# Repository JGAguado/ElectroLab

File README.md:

[![Documentation Status][documentation-shield]][documentation]
[![GitHub Release][releases-shield]][releases]
[![License][license-shield]](LICENSE)
[![BuyIt][buyit-shield]][elecrow]

[![Project Maintenance][maintenance-shield]][maintenance]
[![BuyMeCoffee][buymecoffee-shield]][buymecoffee]

# ElectroLab

The ElectroLab board is an electronic trainer designed for educational purposes. It should be considered as a beginner-friendly guided solution for learning practical electronics where no prior knowledge is required.

With its big set of integrated components, the ElectroLab offers a very powerful and versatile platform for building up your electronic circuits in very few steps.

[documentation-shield]: https://readthedocs.org/projects/electrolab/badge/?version=latest&style=for-the-badge
[documentation]: https://electrolab.readthedocs.io/en/v3/

[releases-shield]: https://img.shields.io/github/release/JGAguado/ElectroLab.svg?style=for-the-badge
[releases]: https://github.com/JGAguado/ElectroLab/releases

[license-shield]: https://img.shields.io/badge/License-CC%20BY--NC--SA%204.0-lightgrey.svg?style=for-the-badge

[maintenance-shield]: https://img.shields.io/badge/maintainer-J.%20G.%20Aguado-blue.svg?style=for-the-badge
[maintenance]: https://github.com/JGAguado

[buymecoffee-shield]: https://img.shields.io/badge/buy%20me%20a%20coffee-support-yellow.svg?style=for-the-badge
[buymecoffee]: https://www.buymeacoffee.com/J.G.Aguado

[buyit-shield]: https://img.shields.io/badge/get%20it%20on-elecrow-399BD7.svg?style=for-the-badge
[elecrow]: https://www.elecrow.com/electrolab.html

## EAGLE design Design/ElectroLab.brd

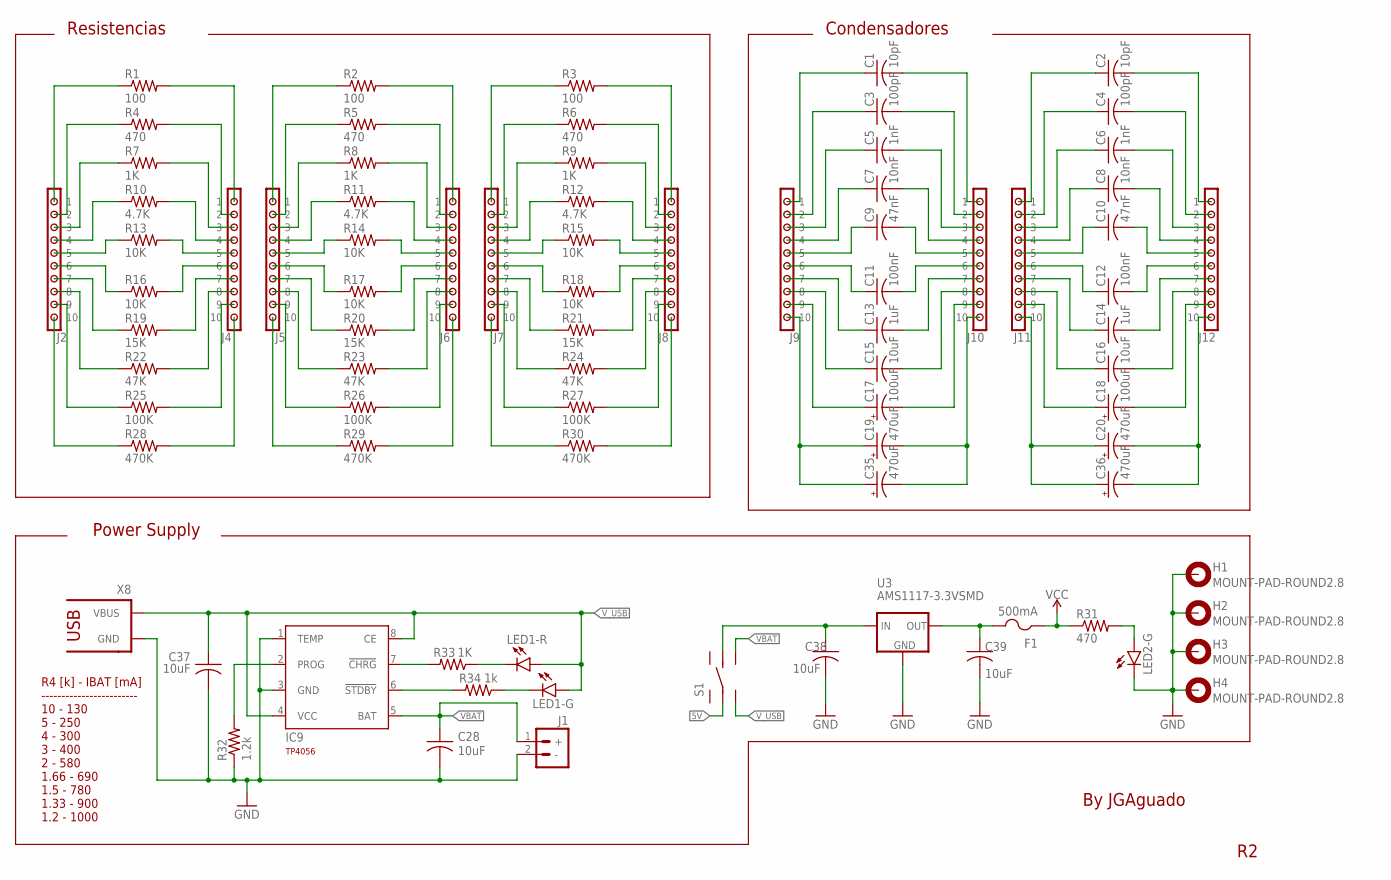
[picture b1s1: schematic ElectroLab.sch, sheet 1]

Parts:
C1, C2: 10pF; 0603
C3, C4: 100pF; 0603
C5, C6: 1nF; 0603
C7, C8: 10nF; 0603
C9, C10: 47nF; 0603
C11, C12: 100nF; 0603
C13, C14: 1uF; 0603
C15, C16: 10uF; 0603
C17, C18: 100uF; B/3528-21R; LCSC C16133
C19, C20, C35, C36: 470uF; D/7343-31R
C28, C37, C38, C39: 10uF; C0603
F1: 500mA; R1206; LCSC C355568
H1, H2, H3, H4: MOUNT-PAD-ROUND2.8; 2,8-PAD
IC9: TP4056; SOT23-8; LCSC C16581
J1: BAT_CONN-JST-2MM-SMT; JST-2-SMD; LCSC C3029440
J2, J4, J5, J6, J7, J8, J9, J10, J11, J12: CONN_10"; 1X10
LED1, LED2: E6CC1205RYGC2UDA; BICOLOR_LED
R1, R2, R3: 100; 0603
R4, R5, R6, R31: 470; 0603
R7, R8, R9, R33: 1K; 0603
R10, R11, R12: 4.7K; 0603
R13, R14, R15, R16, R17, R18: 10K; 0603
R19, R20, R21: 15K; 0603
R22, R23, R24: 47K; 0603
R25, R26, R27: 100K; 0603
R28, R29, R30: 470K; 0603
R32: 1.2k; R0603
R34: 1k; 0603
S1: DPDT_JS202011CQN
U3: AMS1117-3.3VSMD; SOT223
X8: USB-C-POWER

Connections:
5V: S1.2 (LC); also elsewhere on the board
GND: C28.2, C37.2, C38.2, C39.2, H1.B2,8, H2.B2,8, H3.B2,8, H4.B2,8, IC9.1 (TEMP), IC9.3 (GND), J1.2 (-), LED2.1 (C), R32.1, U3.1 (GND), X8.GND; also elsewhere on the board
unnamed: J2.1, R1.1
unnamed: J2.2, R4.1
unnamed: J2.3, R7.1
unnamed: J2.4, R10.1
unnamed: J2.5, R13.1
unnamed: J2.6, R16.1
unnamed: J2.7, R19.1
unnamed: J2.8, R22.1
unnamed: J2.9, R25.1
unnamed: J2.10, R28.1
unnamed: J4.10, R28.2
unnamed: J4.9, R25.2
unnamed: J4.8, R22.2
unnamed: J4.7, R19.2
unnamed: J4.5, R13.2
unnamed: J4.6, R16.2
unnamed: J4.4, R10.2
unnamed: J4.3, R7.2
unnamed: J4.2, R4.2
unnamed: J4.1, R1.2
unnamed: J5.1, R2.1
unnamed: J5.2, R5.1
unnamed: J5.3, R8.1
unnamed: J5.4, R11.1
unnamed: J5.5, R14.1
unnamed: J5.6, R17.1
unnamed: J5.7, R20.1
unnamed: J5.8, R23.1
unnamed: J5.9, R26.1
unnamed: J5.10, R29.1
unnamed: J6.10, R29.2
unnamed: J6.9, R26.2
unnamed: J6.8, R23.2
unnamed: J6.7, R20.2
unnamed: J6.6, R17.2
unnamed: J6.5, R14.2
unnamed: J6.4, R11.2
unnamed: J6.3, R8.2
unnamed: J6.2, R5.2
unnamed: J6.1, R2.2
unnamed: J7.1, R3.1
unnamed: J7.2, R6.1
unnamed: J7.3, R9.1
unnamed: J7.4, R12.1
unnamed: J7.5, R15.1
unnamed: J7.6, R18.1
unnamed: J7.7, R21.1
unnamed: J7.8, R24.1
unnamed: J7.9, R27.1
unnamed: J7.10, R30.1
unnamed: J8.10, R30.2
unnamed: J8.9, R27.2
unnamed: J8.8, R24.2
unnamed: J8.7, R21.2
unnamed: J8.6, R18.2
unnamed: J8.5, R15.2
unnamed: J8.4, R12.2
unnamed: J8.3, R9.2
unnamed: J8.2, R6.2
unnamed: J8.1, R3.2
unnamed: C1.1, J9.1
unnamed: C3.1, J9.2
unnamed: C5.1, J9.3
unnamed: C7.1, J9.4
unnamed: C9.1, J9.5
unnamed: C11.1, J9.6
unnamed: C13.1, J9.7
unnamed: C15.1, J9.8
unnamed: C17.+, J9.9
unnamed: C19.+, C35.+, J9.10
unnamed: C1.2, J10.1
unnamed: C3.2, J10.2
unnamed: C5.2, J10.3
unnamed: C7.2, J10.4
unnamed: C9.2, J10.5
unnamed: C11.2, J10.6
unnamed: C13.2, J10.7
unnamed: C15.2, J10.8
unnamed: C17.-, J10.9
unnamed: C19.-, C35.-, J10.10
unnamed: C2.1, J11.1
unnamed: C4.1, J11.2
unnamed: C6.1, J11.3
unnamed: C8.1, J11.4
unnamed: C10.1, J11.5
unnamed: C12.1, J11.6
unnamed: C14.1, J11.7
unnamed: C16.1, J11.8
unnamed: C18.+, J11.9
unnamed: C20.+, C36.+, J11.10
unnamed: C20.-, C36.-, J12.10
unnamed: C18.-, J12.9
unnamed: C16.2, J12.8
unnamed: C14.2, J12.7
unnamed: C12.2, J12.6
unnamed: C10.2, J12.5
unnamed: C8.2, J12.4
unnamed: C6.2, J12.3
unnamed: C4.2, J12.2
unnamed: C2.2, J12.1
unnamed: LED2.2 (A), R31.2
unnamed: IC9.6 (!STDBY), R34.2
unnamed: LED1.4 (C), R33.1
unnamed: LED1.1 (C), R34.1
unnamed: IC9.2 (PROG), R32.2
unnamed: IC9.7 (!CHRG), R33.2
unnamed: C38.1, S1.5 (RC), U3.3 (IN)
VBAT: C28.1, IC9.5 (BAT), J1.1 (+), S1.6 (R2)
VCC: F1.1, R31.1; also elsewhere on the board
VOUT: C39.1, F1.2, U3.2 (OUT)
V_USB: C37.1, IC9.4 (VCC), IC9.8 (CE), LED1.2 (A), LED1.3 (A), S1.3 (L2), X8.VBUS

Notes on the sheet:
By JGAguado
Condensadores
Resistencias
Power Supply
R4 [k] - IBAT [mA] ------------------------ 10 - 130 5 - 250 4 - 300 3 - 400 2 - 580 1.66 - 690 1.5 - 780 1.33 - 900 1.2 - 1000

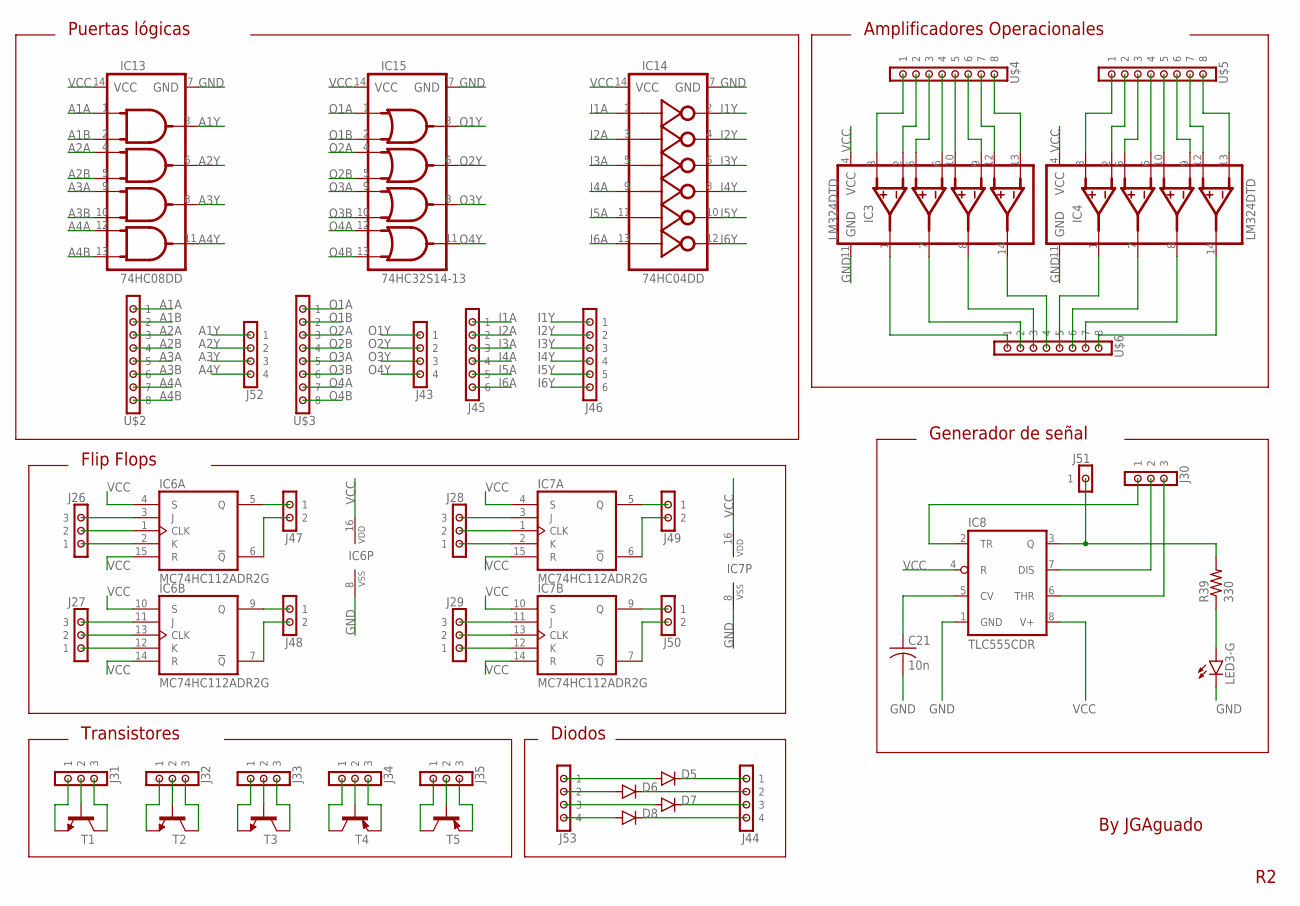
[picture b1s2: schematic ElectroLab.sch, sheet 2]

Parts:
C21: 10n; 0603
D5, D6, D7, D8: LL4148; LL-34
IC3, IC4: LM324DTD; SO14
IC6, IC7: MC74HC112ADR2G; SO16
IC8: TLC555CDR; SO08; LCSC C6986
IC13: 74HC08DD; SO14
IC14: 74HC04DD; SO14
IC15: 74HC32S14-13; SO14; LCSC C176921
J26, J27, J28, J29, J30, J31, J32, J33, J34, J35: CONN_03; 1X03
J43, J44, J52, J53: CONN_04; 1X04
J45, J46: CONN_06; 1X06
J47, J48, J49, J50: CONN_02; 1X02
J51: CONN_01; 1X01
LED3: E6CC1205RYGC2UDA; BICOLOR_LED
R39: 330; 0603
T1: MMBT2222A; SOT23
T2, T3: T_NPNMMBT2222A-1P_CHANGJ_SOT23-BEC; SOT23
T4, T5: T_PNPMMBT5401_CHANGJ_SOT23-BEC; SOT23
U$2, U$3, U$4, U$5, U$6: CONN_08; 1X08

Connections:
A1A: IC13.1 (1A), U$2.1; also elsewhere on the board
A1B: IC13.2 (1B), U$2.2; also elsewhere on the board
A1Y: IC13.3 (1Y), J52.1
A2A: IC13.4 (2A), U$2.3; also elsewhere on the board
A2B: IC13.5 (2B), U$2.4; also elsewhere on the board
A2Y: IC13.6 (2Y), J52.2
A3A: IC13.9 (3A), U$2.5; also elsewhere on the board
A3B: IC13.10 (3B), U$2.6; also elsewhere on the board
A3Y: IC13.8 (3Y), J52.3
A4A: IC13.12 (4A), U$2.7; also elsewhere on the board
A4B: IC13.13 (4B), U$2.8; also elsewhere on the board
A4Y: IC13.11 (4Y), J52.4
GND: C21.2, IC3.11 (GND), IC4.11 (GND), IC6.8 (VSS), IC7.8 (VSS), IC8.1 (GND), IC13.7 (GND), IC14.7 (GND), IC15.7 (GND), LED3.1 (C); also elsewhere on the board
I1A: IC14.1 (1A), J45.1; also elsewhere on the board
I1Y: IC14.2 (1Y), J46.1
I2A: IC14.3 (2A), J45.2; also elsewhere on the board
I2Y: IC14.4 (2Y), J46.2
I3A: IC14.5 (3A), J45.3; also elsewhere on the board
I3Y: IC14.6 (3Y), J46.3
I4A: IC14.9 (4A), J45.4; also elsewhere on the board
I4Y: IC14.8 (4Y), J46.4
I5A: IC14.11 (5A), J45.5; also elsewhere on the board
I5Y: IC14.10 (5Y), J46.5
I6A: IC14.13 (6A), J45.6; also elsewhere on the board
I6Y: IC14.12 (6Y), J46.6
unnamed: D8.A, J53.4
unnamed: D8.C, J44.4
unnamed: D5.A, J53.1
unnamed: IC6.5 (Q), J47.1
unnamed: IC6.9 (Q), J48.1
unnamed: IC7.5 (Q), J49.1
unnamed: IC7.9 (Q), J50.1
unnamed: LED3.2 (A), R39.1
unnamed: IC3.3 (1+), U$4.1
unnamed: IC3.2 (1-), U$4.2
unnamed: IC3.5 (2+), U$4.3
unnamed: IC3.6 (2-), U$4.4
unnamed: IC3.10 (3+), U$4.5
unnamed: IC3.9 (3-), U$4.6
unnamed: IC3.12 (4+), U$4.7
unnamed: IC3.13 (4-), U$4.8
unnamed: IC4.3 (1+), U$5.1
unnamed: IC6.2 (K), J26.1
unnamed: IC6.1 (CLK), J26.2
unnamed: IC6.3 (J), J26.3
unnamed: IC6.12 (K), J27.1
unnamed: IC6.13 (CLK), J27.2
unnamed: IC6.11 (J), J27.3
unnamed: IC7.2 (K), J28.1
unnamed: IC7.1 (CLK), J28.2
unnamed: IC7.3 (J), J28.3
unnamed: IC7.12 (K), J29.1
unnamed: IC7.13 (CLK), J29.2
unnamed: IC7.11 (J), J29.3
unnamed: IC6.6 (!Q), J47.2
unnamed: IC6.7 (!Q), J48.2
unnamed: IC7.6 (!Q), J49.2
unnamed: IC7.7 (!Q), J50.2
unnamed: D7.A, J53.3
unnamed: D6.A, J53.2
unnamed: IC4.2 (1-), U$5.2
unnamed: IC4.5 (2+), U$5.3
unnamed: IC4.6 (2-), U$5.4
unnamed: IC4.10 (3+), U$5.5
unnamed: IC4.9 (3-), U$5.6
unnamed: IC4.12 (4+), U$5.7
unnamed: IC4.13 (4-), U$5.8
unnamed: IC3.1 (1Y), U$6.1
unnamed: IC3.7 (2Y), U$6.2
unnamed: IC3.8 (3Y), U$6.3
unnamed: IC3.14 (4Y), U$6.4
unnamed: IC4.1 (1Y), U$6.5
unnamed: IC4.7 (2Y), U$6.6
unnamed: D5.C, J44.1
unnamed: IC4.8 (3Y), U$6.7
unnamed: IC4.14 (4Y), U$6.8
unnamed: D6.C, J44.2
unnamed: D7.C, J44.3
unnamed: J31.1, T1.2 (E)
unnamed: J31.2, T1.1 (B)
unnamed: J31.3, T1.3 (C)
unnamed: J32.1, T2.2 (E)
unnamed: J32.2, T2.1 (B)
unnamed: J32.3, T2.3 (C)
unnamed: J33.1, T3.2 (E)
unnamed: J33.2, T3.1 (B)
unnamed: J33.3, T3.3 (C)
unnamed: J34.1, T4.3 (C)
unnamed: J34.2, T4.1 (B)
unnamed: J34.3, T4.2 (E)
unnamed: J35.1, T5.3 (C)
unnamed: J35.2, T5.1 (B)
unnamed: J35.3, T5.2 (E)
unnamed: IC8.2 (TR), J30.1
unnamed: IC8.3 (Q), J51.1, R39.2
unnamed: C21.1, IC8.5 (CV)
unnamed: IC8.7 (DIS), J30.2
unnamed: IC8.6 (THR), J30.3
O1A: IC15.1 (1A), U$3.1; also elsewhere on the board
O1B: IC15.2 (1B), U$3.2; also elsewhere on the board
O1Y: IC15.3 (1Y), J43.1
O2A: IC15.4 (2A), U$3.3; also elsewhere on the board
O2B: IC15.5 (2B), U$3.4; also elsewhere on the board
O2Y: IC15.6 (2Y), J43.2
O3A: IC15.9 (3A), U$3.5; also elsewhere on the board
O3B: IC15.10 (3B), U$3.6; also elsewhere on the board
O3Y: IC15.8 (3Y), J43.3
O4A: IC15.12 (4A), U$3.7; also elsewhere on the board
O4B: IC15.13 (4B), U$3.8; also elsewhere on the board
O4Y: IC15.11 (4Y), J43.4
VCC: IC3.4 (VCC), IC4.4 (VCC), IC6.4 (S), IC6.10 (S), IC6.14 (R), IC6.15 (R), IC6.16 (VDD), IC7.4 (S), IC7.10 (S), IC7.14 (R), IC7.15 (R), IC7.16 (VDD), IC8.4 (R), IC8.8 (V+), IC13.14 (VCC), IC14.14 (VCC), IC15.14 (VCC); also elsewhere on the board

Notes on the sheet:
Puertas lógicas
Amplificadores Operacionales
Flip Flops
Transistores
Diodos
Generador de señal
By JGAguado

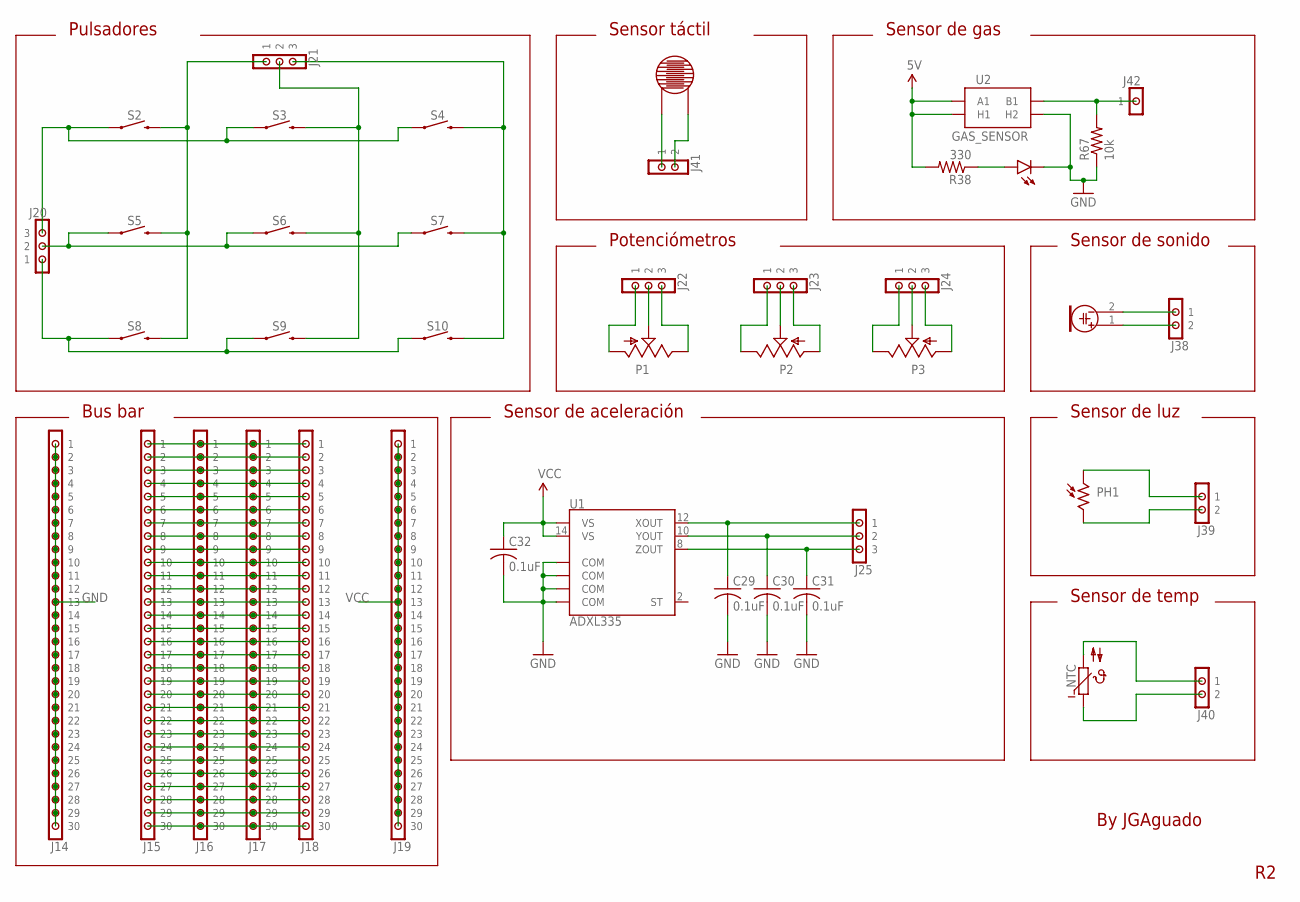
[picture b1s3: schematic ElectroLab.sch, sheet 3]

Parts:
C29, C30, C31, C32: 0.1uF; 0603
J14, J15, J16, J17, J18, J19: CONN_30; 1X30
J20, J21, J22, J23, J24, J25: CONN_03; 1X03
J38, J39, J40, J41: CONN_02; 1X02
J42: CONN_01; 1X01
LED13: E6CC1205RYGC2UDA; BICOLOR_LED
MIC: MICROPHONE
NTC: THERMISTOR; NTC
P1: SLIDE_POT_20MM; RS201111J011
P2, P3: ALPS_RK09K_VERTICAL
PH1: PHOTORESISTOR; GL5516
R38: 330; 0603
R67: 10k; 0603
S2, S3, S4, S5, S6, S7, S8, S9, S10: MOMENTARY-SWITCH-SPST-PTH-6.0MM; TACTILE_SWITCH_PTH_6.0MM
U1: ADXL335; LFCSP-16-4X4; LCSC C34439
U2: GAS_SENSOR
U$16: RESISTIVE_SENSOR_PAD

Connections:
5V: R38.2, U2.A1, U2.HA (H1); also elsewhere on the board
GND: C29.2, C30.2, C31.2, C32.2, J14.1, J14.2, J14.3, J14.4, J14.5, J14.6, J14.7, J14.8, J14.9, J14.10, J14.11, J14.12, J14.13, J14.14, J14.15, J14.16, J14.17, J14.18, J14.19, J14.20, J14.21, J14.22, J14.23, J14.24, J14.25, J14.26, J14.27, J14.28, J14.29, J14.30, LED13.1 (C), R67.1, U1.3 (COM), U1.5 (COM), U1.6 (COM), U1.7 (COM), U2.HB (H2); also elsewhere on the board
unnamed: J42.1, R67.2, U2.B1
unnamed: LED13.2 (A), R38.1
unnamed: J41.2, U$16.0
unnamed: J41.1, U$16.1
unnamed: J15.24, J16.24, J17.24, J18.24
unnamed: J15.30, J16.30, J17.30, J18.30
unnamed: J15.29, J16.29, J17.29, J18.29
unnamed: J15.28, J16.28, J17.28, J18.28
unnamed: J15.27, J16.27, J17.27, J18.27
unnamed: J15.26, J16.26, J17.26, J18.26
unnamed: J15.25, J16.25, J17.25, J18.25
unnamed: J15.23, J16.23, J17.23, J18.23
unnamed: J15.22, J16.22, J17.22, J18.22
unnamed: J15.21, J16.21, J17.21, J18.21
unnamed: J15.20, J16.20, J17.20, J18.20
unnamed: J15.19, J16.19, J17.19, J18.19
unnamed: J15.18, J16.18, J17.18, J18.18
unnamed: J15.17, J16.17, J17.17, J18.17
unnamed: J15.16, J16.16, J17.16, J18.16
unnamed: J15.15, J16.15, J17.15, J18.15
unnamed: J15.14, J16.14, J17.14, J18.14
unnamed: J15.13, J16.13, J17.13, J18.13
unnamed: J15.12, J16.12, J17.12, J18.12
unnamed: J15.11, J16.11, J17.11, J18.11
unnamed: J15.10, J16.10, J17.10, J18.10
unnamed: J15.9, J16.9, J17.9, J18.9
unnamed: J15.8, J16.8, J17.8, J18.8
unnamed: J15.7, J16.7, J17.7, J18.7
unnamed: J15.6, J16.6, J17.6, J18.6
unnamed: J15.5, J16.5, J17.5, J18.5
unnamed: J15.4, J16.4, J17.4, J18.4
unnamed: J15.3, J16.3, J17.3, J18.3
unnamed: J15.2, J16.2, J17.2, J18.2
unnamed: J15.1, J16.1, J17.1, J18.1
unnamed: J21.1, S2.3 (2), S5.3 (2), S8.3 (2)
unnamed: J21.2, S3.3 (2), S6.3 (2), S9.3 (2)
unnamed: J39.1, PH1.1
unnamed: J39.2, PH1.3
unnamed: J40.1, NTC.2
unnamed: J23.1, P2.3
unnamed: J23.2, P2.2
unnamed: J23.3, P2.1
unnamed: J22.1, P1.3
unnamed: J22.2, P1.2
unnamed: J22.3, P1.1
unnamed: J24.1, P3.3
unnamed: J24.2, P3.2
unnamed: J24.3, P3.1
unnamed: J38.1, MIC.2
unnamed: J38.2, MIC.1
unnamed: J20.3, S2.1, S3.1, S4.1
unnamed: J40.2, NTC.1
unnamed: J20.2, S5.1, S6.1, S7.1
unnamed: J21.3, S4.3 (2), S7.3 (2), S10.3 (2)
unnamed: J20.1, S8.1, S9.1, S10.1
VCC: C32.1, J19.1, J19.2, J19.3, J19.4, J19.5, J19.6, J19.7, J19.8, J19.9, J19.10, J19.11, J19.12, J19.13, J19.14, J19.15, J19.16, J19.17, J19.18, J19.19, J19.20, J19.21, J19.22, J19.23, J19.24, J19.25, J19.26, J19.27, J19.28, J19.29, J19.30, U1.14 (VS), U1.15 (VS); also elsewhere on the board
X+: C29.1, J25.1, U1.12 (XOUT)
Y+: C30.1, J25.2, U1.10 (YOUT)
Z+: C31.1, J25.3, U1.8 (ZOUT)

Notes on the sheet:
Pulsadores
Potenciómetros
Sensor táctil
Sensor de luz
Sensor de sonido
Sensor de temp
Sensor de aceleración
Bus bar
By JGAguado
Sensor de gas

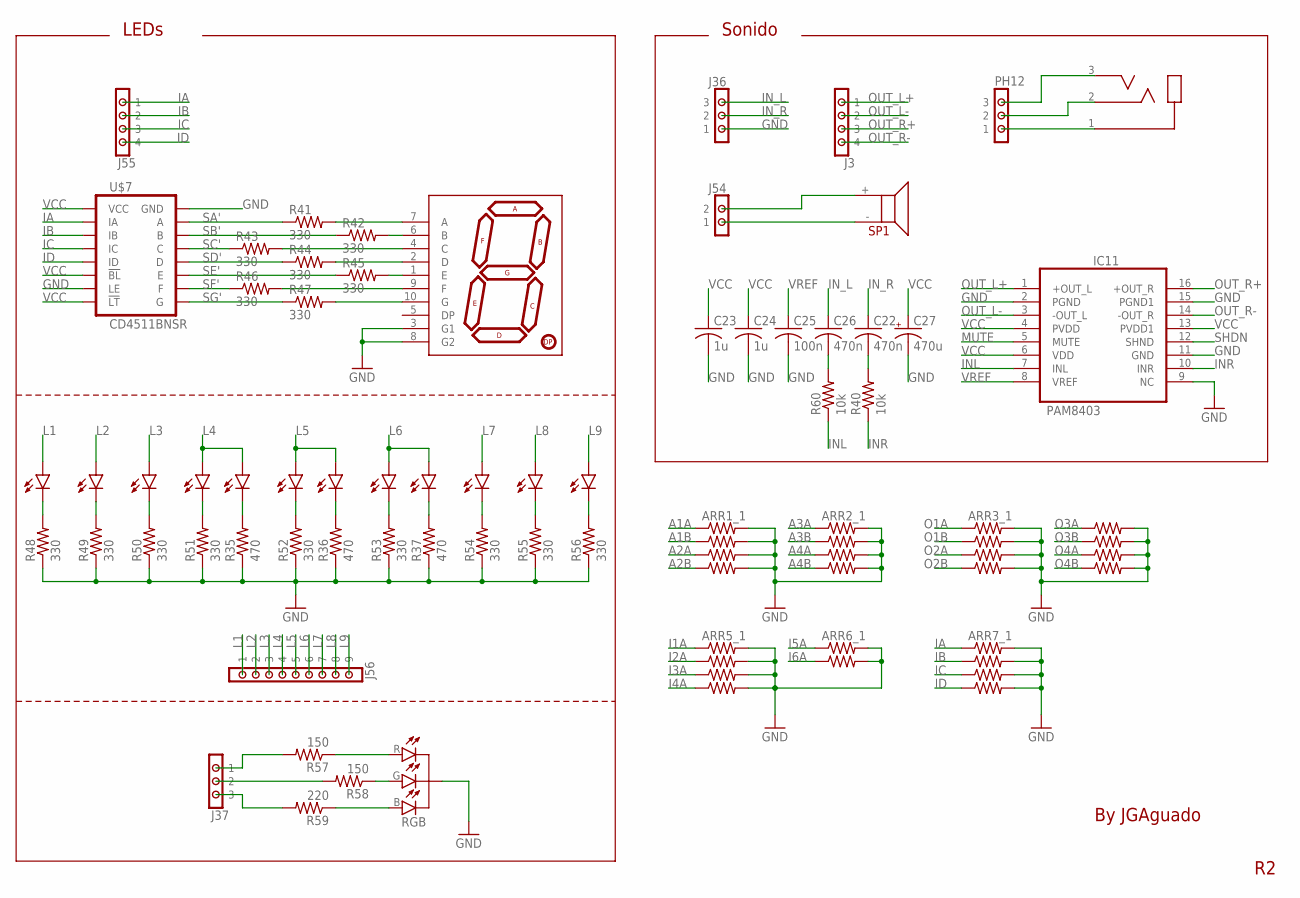
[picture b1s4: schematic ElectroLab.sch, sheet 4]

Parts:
ARR1, ARR2, ARR3, ARR4, ARR5, ARR6, ARR7: 4_RES_ARRAY_R06031KOHM; 0603-ARC
C22, C26: 470n; 0603
C23, C24: 1u; 0603
C25: 100n; 0603
C27: 470u; D/7343-31R; LCSC C7229
IC11: PAM8403; SOP-16
J3, J55: CONN_04; 1X04
J36, J37: CONN_03; 1X03
J54: CONN_02; 1X02
J56: CONN_09; 1X09
JACK: AUDIO_JACK_MONO_3.5_3P; HC-PJ-320A-3P-D
LED4, LED5, LED6, LED7, LED8, LED9, LED10, LED11, LED12: E6CC1205RYGC2UDA; BICOLOR_LED
PH12: CONN_03; 1X03
R35, R36, R37: 470; 0603
R40, R60: 10k; 0603
R41, R42, R43, R44, R45, R46, R47, R48, R49, R50, R51, R52, R53, R54, R55, R56: 330; 0603
R57, R58: 150; 0603
R59: 220; 0603
RGB: CLEAR; LED-RGB-THRU
SP1: SPEAKERFS1508MB0810-H8.0; FS1508MB0810-H8.0
U$1: FJ5101AG; 7-SEGMENT
U$7: CD4511BNSR; SO16

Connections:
A1A: ARR1.1; also elsewhere on the board
A1B: ARR1.2 (1); also elsewhere on the board
A2A: ARR1.3 (1); also elsewhere on the board
A2B: ARR1.4 (1); also elsewhere on the board
A3A: ARR2.1; also elsewhere on the board
A3B: ARR2.2 (1); also elsewhere on the board
A4A: ARR2.3 (1); also elsewhere on the board
A4B: ARR2.4 (1); also elsewhere on the board
B: J37.3, R59.2
G: J37.2, R58.2
GND: ARR1.5 (2), ARR1.6 (2), ARR1.7 (2), ARR1.8 (2), ARR2.5 (2), ARR2.6 (2), ARR2.7 (2), ARR2.8 (2), ARR3.5 (2), ARR3.6 (2), ARR3.7 (2), ARR3.8 (2), ARR4.5 (2), ARR4.6 (2), ARR4.7 (2), ARR4.8 (2), ARR5.5 (2), ARR5.6 (2), ARR5.7 (2), ARR5.8 (2), ARR6.7 (2), ARR6.8 (2), ARR7.5 (2), ARR7.6 (2), ARR7.7 (2), ARR7.8 (2), C23.2, C24.2, C25.2, C27.-, IC11.2 (PGND), IC11.9 (NC), IC11.11 (GND), IC11.15 (PGND1), J36.1, R35.1, R36.1, R37.1, R48.1, R49.1, R50.1, R51.1, R52.1, R53.1, R54.1, R55.1, R56.1, RGB.C, U$1.3 (G1), U$1.8 (G2), U$7.5 (LE), U$7.8 (GND); also elsewhere on the board
I1A: ARR5.1; also elsewhere on the board
I2A: ARR5.2 (1); also elsewhere on the board
I3A: ARR5.3 (1); also elsewhere on the board
I4A: ARR5.4 (1); also elsewhere on the board
I5A: ARR6.1; also elsewhere on the board
I6A: ARR6.2 (1); also elsewhere on the board
IA: ARR7.1, J55.1, U$7.7 (IA)
IB: ARR7.2 (1), J55.2, U$7.1 (IB)
IC: ARR7.3 (1), J55.3, U$7.2 (IC)
ID: ARR7.4 (1), J55.4, U$7.6 (ID)
INL: IC11.7 (INL), R60.1
INR: IC11.10 (INR), R40.1
IN_L: C26.1, J36.3
IN_R: C22.1, J36.2
L1: J56.1, LED4.2 (A)
L2: J56.2, LED5.2 (A)
L3: J56.3, LED6.2 (A)
L4: J56.4, LED7.2 (A), LED7.3 (A)
L5: J56.5, LED8.2 (A), LED8.3 (A)
L6: J56.6, LED9.2 (A), LED9.3 (A)
L7: J56.7, LED10.3 (A)
L8: J56.8, LED11.3 (A)
L9: J56.9, LED12.3 (A)
MUTE: IC11.5 (MUTE)
unnamed: JACK.2, PH12.2
unnamed: JACK.1, PH12.1
unnamed: R58.1, RGB.G
unnamed: LED4.1 (C), R48.2
unnamed: C26.2, R60.2
unnamed: C22.2, R40.2
unnamed: LED5.1 (C), R49.2
unnamed: LED6.1 (C), R50.2
unnamed: LED7.1 (C), R51.2
unnamed: LED8.1 (C), R52.2
unnamed: LED9.1 (C), R53.2
unnamed: LED7.4 (C), R35.2
unnamed: LED8.4 (C), R36.2
unnamed: LED9.4 (C), R37.2
unnamed: LED10.4 (C), R54.2
unnamed: LED11.4 (C), R55.2
unnamed: LED12.4 (C), R56.2
unnamed: J54.2, SP1.+
unnamed: JACK.3, PH12.3
unnamed: J54.1, SP1.-
unnamed: R57.1, RGB.R
unnamed: R59.1, RGB.B
O1A: ARR3.1; also elsewhere on the board
O1B: ARR3.2 (1); also elsewhere on the board
O2A: ARR3.3 (1); also elsewhere on the board
O2B: ARR3.4 (1); also elsewhere on the board
O3A: ARR4.1; also elsewhere on the board
O3B: ARR4.2 (1); also elsewhere on the board
O4A: ARR4.3 (1); also elsewhere on the board
O4B: ARR4.4 (1); also elsewhere on the board
OUT_L+: IC11.1 (+OUT_L), J3.1
OUT_L-: IC11.3 (-OUT_L), J3.2
OUT_R+: IC11.16 (+OUT_R), J3.3
OUT_R-: IC11.14 (-OUT_R), J3.4
R: J37.1, R57.2
SA: R41.2, U$1.7 (A)
SA': R41.1, U$7.13 (A)
SB: R42.2, U$1.6 (B)
SB': R42.1, U$7.12 (B)
SC: R43.2, U$1.4 (C)
SC': R43.1, U$7.11 (C)
SD: R44.2, U$1.2 (D)
SD': R44.1, U$7.10 (D)
SE: R45.2, U$1.1 (E)
SE': R45.1, U$7.9 (E)
SF: R46.2, U$1.9 (F)
SF': R46.1, U$7.15 (F)
SG: R47.2, U$1.10 (G)
SG': R47.1, U$7.14 (G)
SHDN: IC11.12 (SHND)
VCC: C23.1, C24.1, C27.+, IC11.4 (PVDD), IC11.6 (VDD), IC11.13 (PVDD1), U$7.3 (!LT), U$7.4 (!BL), U$7.16 (VCC); also elsewhere on the board
VREF: C25.1, IC11.8 (VREF)

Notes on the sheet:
Sonido
LEDs
By JGAguado

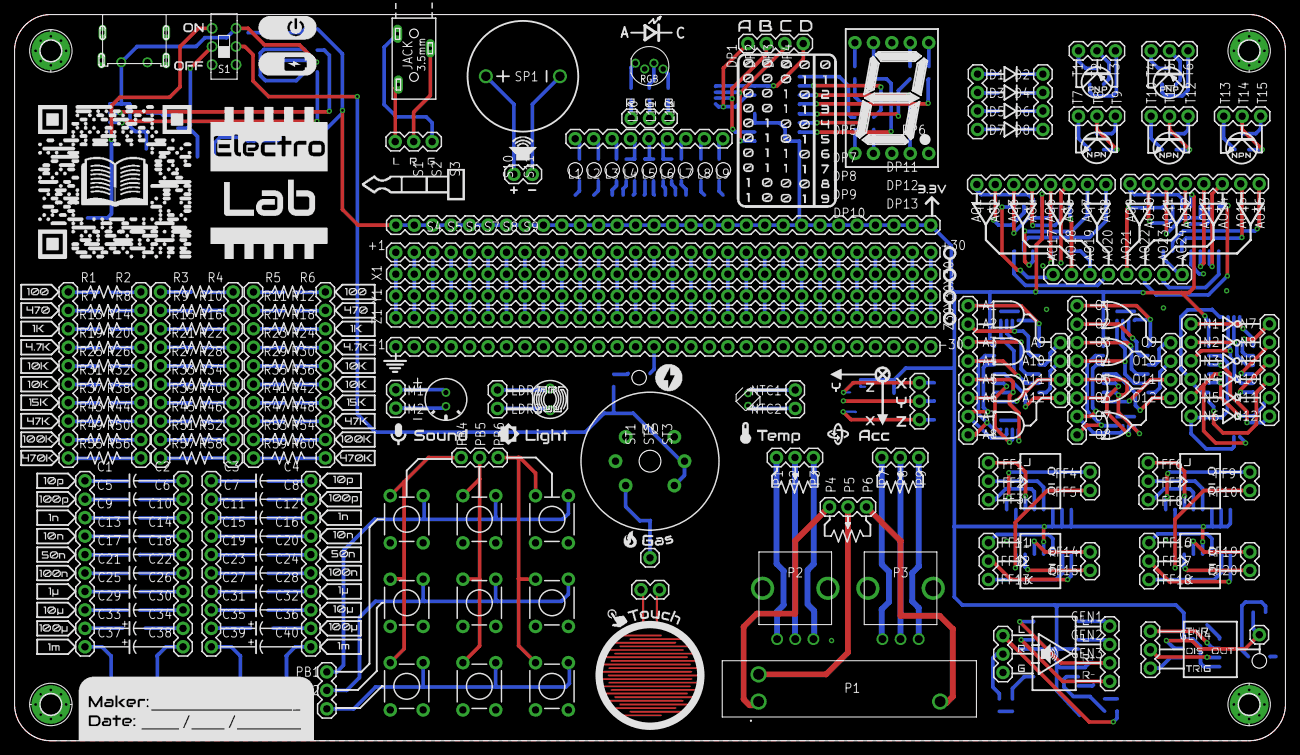
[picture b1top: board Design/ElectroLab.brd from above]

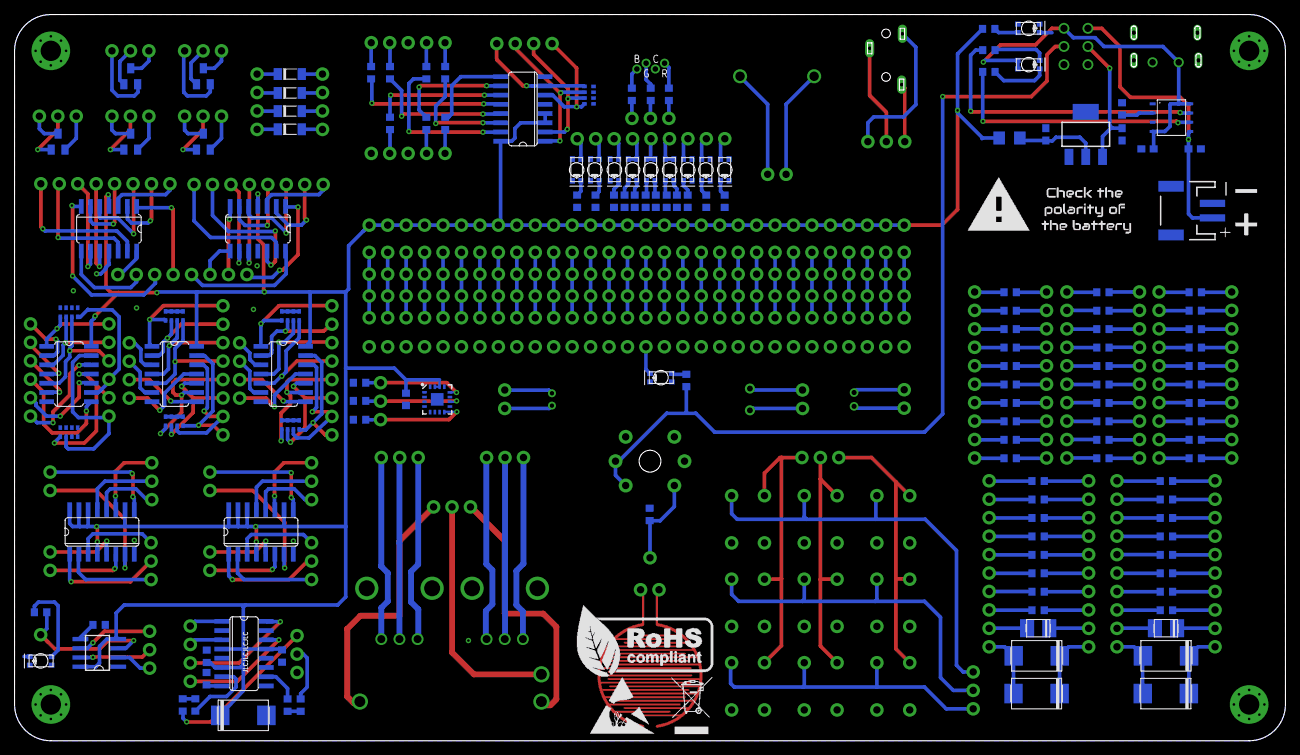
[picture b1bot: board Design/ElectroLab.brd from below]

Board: 2 copper layers, 175.0 x 100.0 mm, 229 parts (142 on the bottom side), 341 nets.

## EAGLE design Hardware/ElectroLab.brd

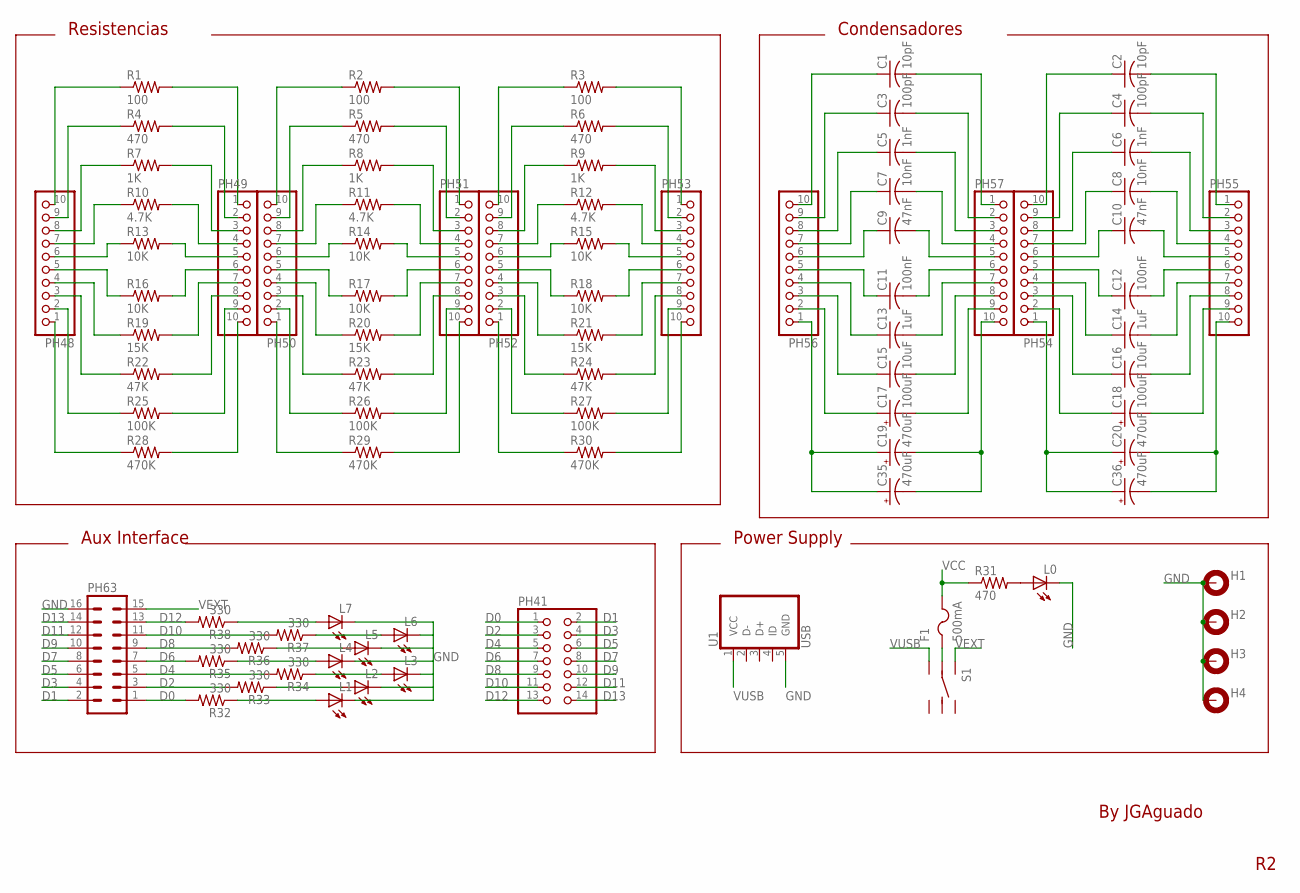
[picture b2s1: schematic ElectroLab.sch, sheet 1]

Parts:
C1, C2: 10pF; C1206
C3, C4: 100pF; C1206
C5, C6: 1nF; C1206
C7, C8: 10nF; C1206
C9, C10: 47nF; C1206
C11, C12: 100nF; C1206
C13, C14: 1uF; C1206
C15, C16: 10uF; C1206
C17, C18: 100uF; A/3216-18R
C19, C20, C35, C36: 470uF; D/7343-31R
F1: 500mA; R1206
H1, H2, H3, H4: MOUNT-PAD-ROUND2.8; 2,8-PAD
L0, L1, L2, L3, L4, L5, L6, L7: LEDSMT1206; 1206
PH41: PINHD-2X7; 2X07
PH48, PH49, PH50, PH51, PH52, PH53, PH54, PH55, PH56, PH57: PINHD-1X10; 1X10-BIG
PH63: MA08-2
R1, R2, R3: 100; R1206
R4, R5, R6, R31: 470; R1206
R7, R8, R9: 1K; R1206
R10, R11, R12: 4.7K; R1206
R13, R14, R15, R16, R17, R18: 10K; R1206
R19, R20, R21: 15K; R1206
R22, R23, R24: 47K; R1206
R25, R26, R27: 100K; R1206
R28, R29, R30: 470K; R1206
R32, R33, R34, R35, R36, R37, R38: 330; R1206
S1: DPDT_JS202011CQN
U1: USB; FCI-10103594-0001LF

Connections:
D0: PH41.1, PH63.1, R32.2
D1: PH41.2, PH63.2
D2: PH41.3, PH63.3, R33.2
D3: PH41.4, PH63.4
D4: PH41.5, PH63.5, R34.2
D5: PH41.6, PH63.6
D6: PH41.7, PH63.7, R35.2
D7: PH41.8, PH63.8
D8: PH41.9, PH63.9, R36.2
D9: PH41.10, PH63.10
D10: PH41.11, PH63.11, R37.2
D11: PH41.12, PH63.12
D12: PH41.13, PH63.13, R38.2
D13: PH41.14, PH63.14
GND: H1.B2,8, H2.B2,8, H3.B2,8, H4.B2,8, L0.C, L1.C, L2.C, L3.C, L4.C, L5.C, L6.C, L7.C, PH63.16, U1.5 (GND); also elsewhere on the board
unnamed: PH48.10, R1.1
unnamed: PH48.9, R4.1
unnamed: PH48.8, R7.1
unnamed: PH48.7, R10.1
unnamed: PH48.6, R13.1
unnamed: PH48.5, R16.1
unnamed: PH48.4, R19.1
unnamed: PH48.3, R22.1
unnamed: PH48.2, R25.1
unnamed: PH48.1, R28.1
unnamed: PH49.10, R28.2
unnamed: PH49.9, R25.2
unnamed: PH49.8, R22.2
unnamed: PH49.7, R19.2
unnamed: PH49.5, R13.2
unnamed: PH49.6, R16.2
unnamed: PH49.4, R10.2
unnamed: PH49.3, R7.2
unnamed: PH49.2, R4.2
unnamed: PH49.1, R1.2
unnamed: PH50.10, R2.1
unnamed: PH50.9, R5.1
unnamed: PH50.8, R8.1
unnamed: PH50.7, R11.1
unnamed: PH50.6, R14.1
unnamed: PH50.5, R17.1
unnamed: PH50.4, R20.1
unnamed: PH50.3, R23.1
unnamed: PH50.2, R26.1
unnamed: PH50.1, R29.1
unnamed: PH51.10, R29.2
unnamed: PH51.9, R26.2
unnamed: PH51.8, R23.2
unnamed: PH51.7, R20.2
unnamed: PH51.6, R17.2
unnamed: PH51.5, R14.2
unnamed: PH51.4, R11.2
unnamed: PH51.3, R8.2
unnamed: PH51.2, R5.2
unnamed: PH51.1, R2.2
unnamed: PH52.10, R3.1
unnamed: PH52.9, R6.1
unnamed: PH52.8, R9.1
unnamed: PH52.7, R12.1
unnamed: PH52.6, R15.1
unnamed: PH52.5, R18.1
unnamed: PH52.4, R21.1
unnamed: PH52.3, R24.1
unnamed: PH52.2, R27.1
unnamed: PH52.1, R30.1
unnamed: PH53.10, R30.2
unnamed: PH53.9, R27.2
unnamed: PH53.8, R24.2
unnamed: PH53.7, R21.2
unnamed: PH53.6, R18.2
unnamed: PH53.5, R15.2
unnamed: PH53.4, R12.2
unnamed: PH53.3, R9.2
unnamed: PH53.2, R6.2
unnamed: PH53.1, R3.2
unnamed: C1.1, PH56.10
unnamed: C3.1, PH56.9
unnamed: C5.1, PH56.8
unnamed: C7.1, PH56.7
unnamed: C9.1, PH56.6
unnamed: C11.1, PH56.5
unnamed: C13.1, PH56.4
unnamed: C15.1, PH56.3
unnamed: C17.+, PH56.2
unnamed: C19.+, C35.+, PH56.1
unnamed: C1.2, PH57.1
unnamed: C3.2, PH57.2
unnamed: C5.2, PH57.3
unnamed: C7.2, PH57.4
unnamed: C9.2, PH57.5
unnamed: C11.2, PH57.6
unnamed: C13.2, PH57.7
unnamed: C15.2, PH57.8
unnamed: C17.-, PH57.9
unnamed: C19.-, C35.-, PH57.10
unnamed: C2.1, PH54.10
unnamed: C4.1, PH54.9
unnamed: C6.1, PH54.8
unnamed: C8.1, PH54.7
unnamed: C10.1, PH54.6
unnamed: C12.1, PH54.5
unnamed: C14.1, PH54.4
unnamed: C16.1, PH54.3
unnamed: C18.+, PH54.2
unnamed: C20.+, C36.+, PH54.1
unnamed: C20.-, C36.-, PH55.10
unnamed: C18.-, PH55.9
unnamed: C16.2, PH55.8
unnamed: C14.2, PH55.7
unnamed: C12.2, PH55.6
unnamed: C10.2, PH55.5
unnamed: C8.2, PH55.4
unnamed: C6.2, PH55.3
unnamed: C4.2, PH55.2
unnamed: C2.2, PH55.1
unnamed: L1.A, R32.1
unnamed: L0.A, R31.2
unnamed: L2.A, R33.1
unnamed: L3.A, R34.1
unnamed: L4.A, R35.1
unnamed: L5.A, R36.1
unnamed: L6.A, R37.1
unnamed: L7.A, R38.1
unnamed: F1.1, S1.2 (LC)
VCC: F1.2, R31.1; also elsewhere on the board
VEXT: PH63.15, S1.1 (L1)
VUSB: S1.3 (L2), U1.1 (VCC)

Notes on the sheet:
By JGAguado
Condensadores
Resistencias
Power Supply
Aux Interface

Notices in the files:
parts and their libraries:
SparkFun-Sensors: Licensing: Creative Commons ShareAlike 4.0 International - https://creativecommons.org/licenses/by-sa/4.0
